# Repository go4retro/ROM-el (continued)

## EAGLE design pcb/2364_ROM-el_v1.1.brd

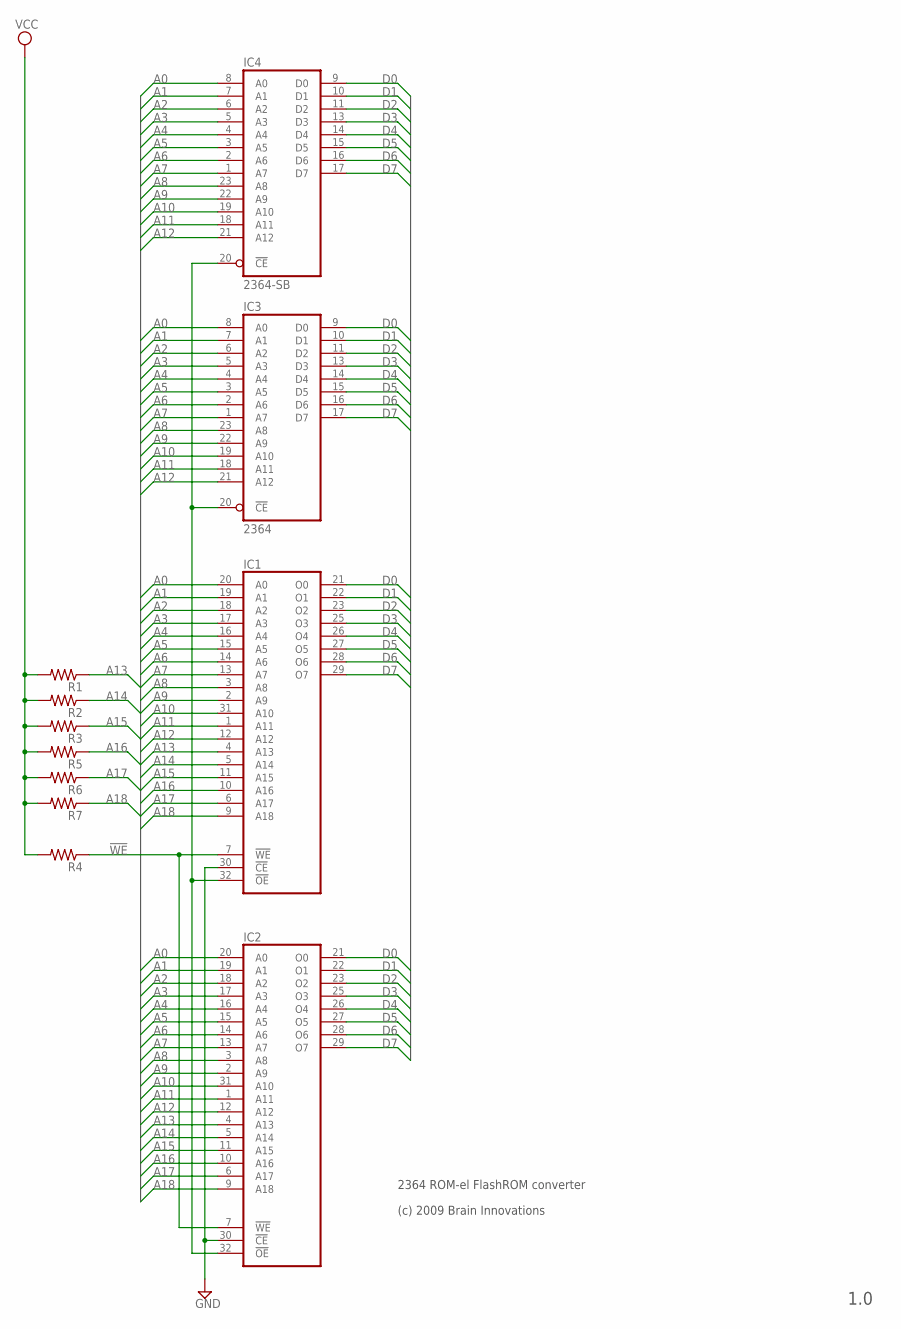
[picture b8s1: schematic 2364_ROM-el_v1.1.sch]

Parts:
IC1: FLASH_RAM4096KB'T'; TSOP32
IC2: FLASH_RAM4096KB'V'; VSOP32
IC3: 2364; DIL24-ROUNDPAD
IC4: 2364-SB; DIL24-SMD-REVERSE
R1, R2, R3, R4, R5, R6, R7: R-US_R0805; R0805

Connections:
!WE: IC1.7 (!WE), IC2.7 (!WE), R4.1
A0: IC1.20 (A0), IC2.20 (A0), IC3.8 (A0), IC4.8 (A0)
A1: IC1.19 (A1), IC2.19 (A1), IC3.7 (A1), IC4.7 (A1)
A2: IC1.18 (A2), IC2.18 (A2), IC3.6 (A2), IC4.6 (A2)
A3: IC1.17 (A3), IC2.17 (A3), IC3.5 (A3), IC4.5 (A3)
A4: IC1.16 (A4), IC2.16 (A4), IC3.4 (A4), IC4.4 (A4)
A5: IC1.15 (A5), IC2.15 (A5), IC3.3 (A5), IC4.3 (A5)
A6: IC1.14 (A6), IC2.14 (A6), IC3.2 (A6), IC4.2 (A6)
A7: IC1.13 (A7), IC2.13 (A7), IC3.1 (A7), IC4.1 (A7)
A8: IC1.3 (A8), IC2.3 (A8), IC3.23 (A8), IC4.23 (A8)
A9: IC1.2 (A9), IC2.2 (A9), IC3.22 (A9), IC4.22 (A9)
A10: IC1.31 (A10), IC2.31 (A10), IC3.19 (A10), IC4.19 (A10)
A11: IC1.1 (A11), IC2.1 (A11), IC3.18 (A11), IC4.18 (A11)
A12: IC1.12 (A12), IC2.12 (A12), IC3.21 (A12), IC4.21 (A12)
A13: IC1.4 (A13), IC2.4 (A13), R1.1
A14: IC1.5 (A14), IC2.5 (A14), R2.1
A15: IC1.11 (A15), IC2.11 (A15), R3.1
A16: IC1.10 (A16), IC2.10 (A16), R5.1
A17: IC1.6 (A17), IC2.6 (A17), R6.1
A18: IC1.9 (A18), IC2.9 (A18), R7.1
D0: IC1.21 (O0), IC2.21 (O0), IC3.9 (D0), IC4.9 (D0)
D1: IC1.22 (O1), IC2.22 (O1), IC3.10 (D1), IC4.10 (D1)
D2: IC1.23 (O2), IC2.23 (O2), IC3.11 (D2), IC4.11 (D2)
D3: IC1.25 (O3), IC2.25 (O3), IC3.13 (D3), IC4.13 (D3)
D4: IC1.26 (O4), IC2.26 (O4), IC3.14 (D4), IC4.14 (D4)
D5: IC1.27 (O5), IC2.27 (O5), IC3.15 (D5), IC4.15 (D5)
D6: IC1.28 (O6), IC2.28 (O6), IC3.16 (D6), IC4.16 (D6)
D7: IC1.29 (O7), IC2.29 (O7), IC3.17 (D7), IC4.17 (D7)
GND: IC1.24 (GND), IC1.30 (!CE), IC2.24 (GND), IC2.30 (!CE), IC3.12 (GND), IC4.12 (GND)
unnamed: IC1.32 (!OE), IC2.32 (!OE), IC3.20 (!CE), IC4.20 (!CE)
VCC: IC1.8 (VCC), IC2.8 (VCC), IC3.24 (VCC), IC4.24 (VCC), R1.2, R2.2, R3.2, R4.2, R5.2, R6.2, R7.2

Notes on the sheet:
(c) 2009 Brain Innovations
2364 ROM-el FlashROM converter
1.0

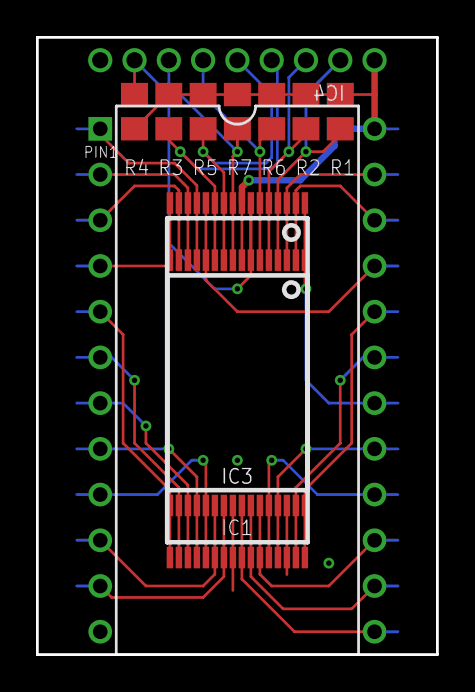
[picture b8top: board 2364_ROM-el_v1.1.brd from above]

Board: 2 copper layers, 22.2 x 34.3 mm, 11 parts (0 on the bottom side), 31 nets.

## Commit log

2025-01-04 Add ROM-el programming adapter
2025-08-09 restructure directories
2025-08-09 Folder cleanup
